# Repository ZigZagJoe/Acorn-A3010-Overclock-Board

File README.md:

# Acorn A3010 Overclock board for early ARM250 machines

Intended for the early machines without an oscillator socket, this enables switching between three speeds: 
Original (clock output is Hi-Z), oscillator on this add in board, or an off-board oscillator such as the 72mhz on the motherboard.

A buffer is used to allow the switch to be located remotely regardless of wire length, and also to minimize loading on the logicboard oscillator (if used). The switch connector is intended for an ON-OFF-ON (or ON-ON-ON) switch.

position 1 (ON) is Hi-Z output (pins 1-2 connected)
position 2 (OFF) or switch disconnected will use onboard oscillator
position 3 (ON) is off-board oscillator (pins 2-3 connected)

The included bracket design clips onto the ventillation slots on the bottom of the case. Unfortunately, it was designed for a specific switch out of my junk box: switch body 16mm L x 7mm W x 7.5mm H, actuator 3mm L x 2.4mm W x 4.2mm H

This is licensed under a
Creative Commons Attribution-NonCommercial 4.0 International License.

You should have received a copy of the license along with this
work. If not, see <https://creativecommons.org/licenses/by-nc/4.0/>.

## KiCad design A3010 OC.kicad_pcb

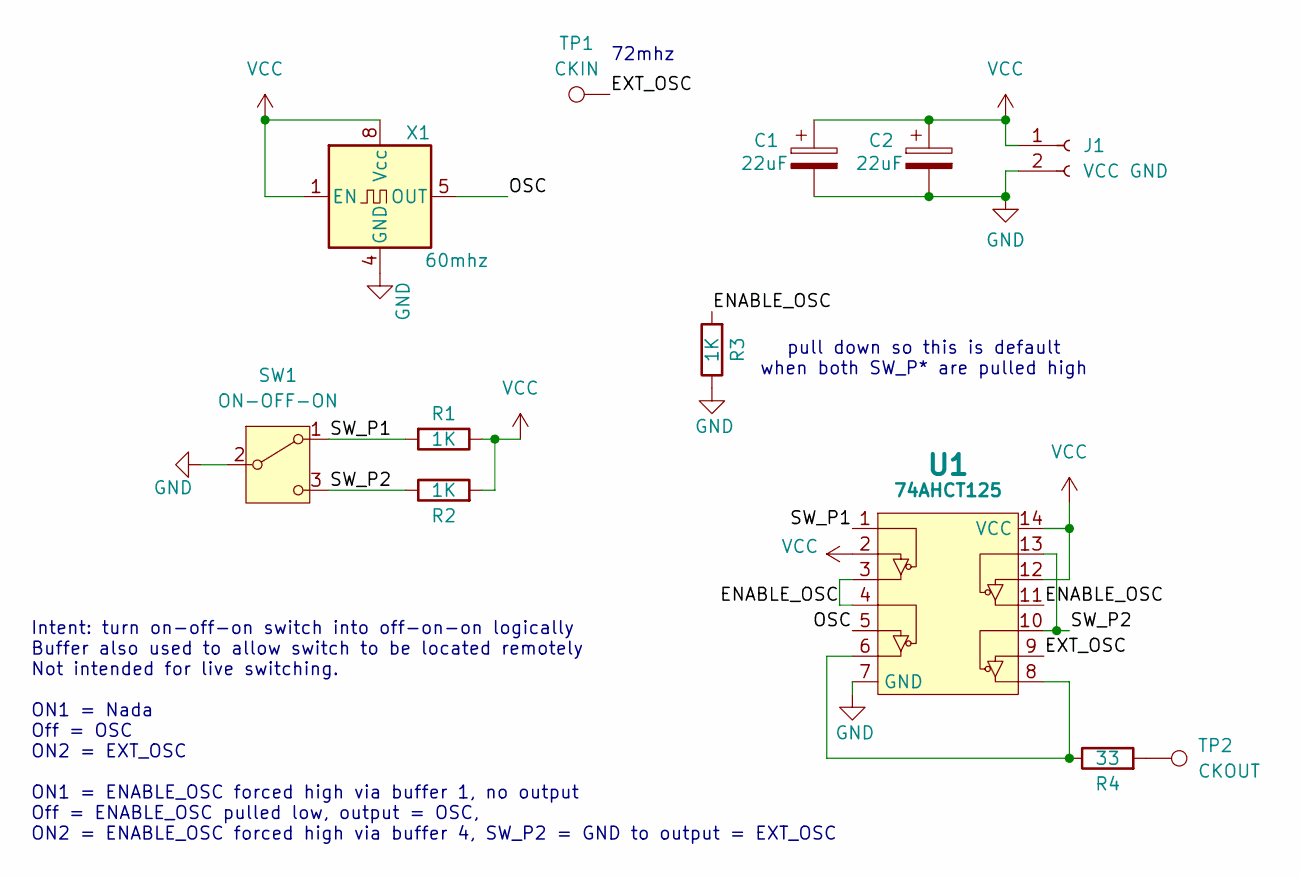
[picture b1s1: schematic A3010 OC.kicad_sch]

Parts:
C1, C2: 22uF; C_0805_2012Metric_Pad1.18x1.45mm_HandSolder; PartNumber CL21A226MAQNNNE; LCSC C45783
J1: VCC GND; PinHeader_1x02_P2.54mm_Vertical
R1, R2, R3: 1K; R_0805_2012Metric_HandSolder_XL; LCSC C23140
R4: 33; R_0805_2012Metric_HandSolder_XL; LCSC C23140
SW1: ON-OFF-ON; PinSocket_1x03_P2.54mm_Vertical
TP1: CKIN; TestPoint_THTPad_D2.0mm_Drill1.0mm
TP2: CKOUT; TestPoint_THTPad_D2.0mm_Drill1.0mm
U1: 74AHCT125; SOIC-14_3.9x8.7mm_P1.27mm_HandSolder; MOUSERPN SN74AHCT125DR
X1: 60mhz; Oscillator_DIP-8_DIP-14; LCSC n/a

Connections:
/ENABLE_OSC: R3.2, U1.3, U1.4, U1.11
/EXT_OSC: TP1.1, U1.9
/OSC: U1.5, X1.5 (OUT)
/SW_P1: R1.2, SW1.1 (A), U1.1
/SW_P2: R2.1, SW1.3 (C), U1.10, U1.13
GND: C1.2, C2.2, J1.2, R3.1, SW1.2 (B), U1.7 (GND), X1.4 (GND)
unnamed: R4.1, U1.6, U1.8
unnamed: R4.2, TP2.1
VCC: C1.1, C2.1, J1.1, R1.1, R2.2, U1.2, U1.12, U1.14 (VCC), X1.1 (EN), X1.8 (Vcc)

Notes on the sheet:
72mhz
Intent: turn on-off-on switch into off-on-on logically Buffer also used to allow switch to be located remotely Not intended for live switching. ON1 = Nada Off = OSC ON2 = EXT_OSC ON1 = ENABLE_OSC forced high via buffer 1, no output Off = ENABLE_OSC pulled low, output = OSC, ON2 = ENABLE_OSC forced 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
pull down so this is default when both SW_P* are pulled high

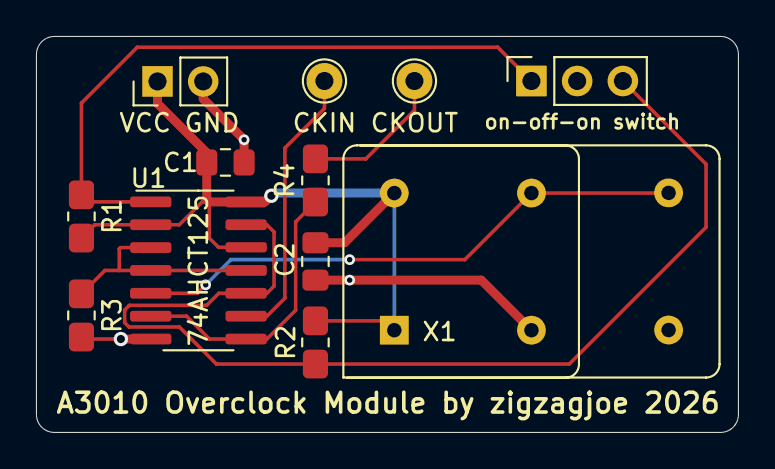
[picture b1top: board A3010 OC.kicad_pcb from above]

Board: 2 copper layers, 39.0 x 22.0 mm, 12 parts (0 on the bottom side), 9 nets.

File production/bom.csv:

Designator,Footprint,Quantity,Value,LCSC Part #
"C1, C2",0805,2,22uF,C45783
J1,PinHeader_1x02_P2.54mm_Vertical,1,VCC GND,
"R1, R2, R3",0805,3,1K,C23140
R4,0805,1,33,C23140
SW1,PinSocket_1x03_P2.54mm_Vertical,1,ON-OFF-ON,
TP1,TestPoint_THTPad_D2.0mm_Drill1.0mm,1,CKIN,
TP2,TestPoint_THTPad_D2.0mm_Drill1.0mm,1,CKOUT,
U1,SOIC-14_3.9x8.7mm_P1.27mm_HandSolder,1,74AHCT125,
X1,Oscillator_DIP-8_DIP-14,1,60mhz,n/a
